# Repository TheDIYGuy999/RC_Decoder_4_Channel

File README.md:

#This is an Arduino 4 channel RC signal to DC motor converter shield
## Features:
- Reads 4 standard RC servo signals and converts them to control 4 DC motors
- Auto channel zero adjustment during setup()
- 5V / 16MHz or 3.3v / 8MHz Pro Micro or Pro Mini
- DRV8833 H-Bridge driver, controlled with my DRV8833 Arduino library
- Motor 1 & 2 can be used to drive a caterpillar vehicle:
* direct mode (2x throttle, one for each caterpillar)
* steering mode means, you have one throttle and one steering input. The speed of the inner wheel can be fully reversed, up to 100%. The vehicle then turns "in place"
* semi caterpillar mode. Same as above, but the speed of the inner wheel can only be reduced about 30%
* arrays for steering behaviour calibration, now with nonlinear mapping
* two additional motor outputs for other vehicle functions

## Usage

See pictures in this repo

(c) 2016 TheDIYGuy999

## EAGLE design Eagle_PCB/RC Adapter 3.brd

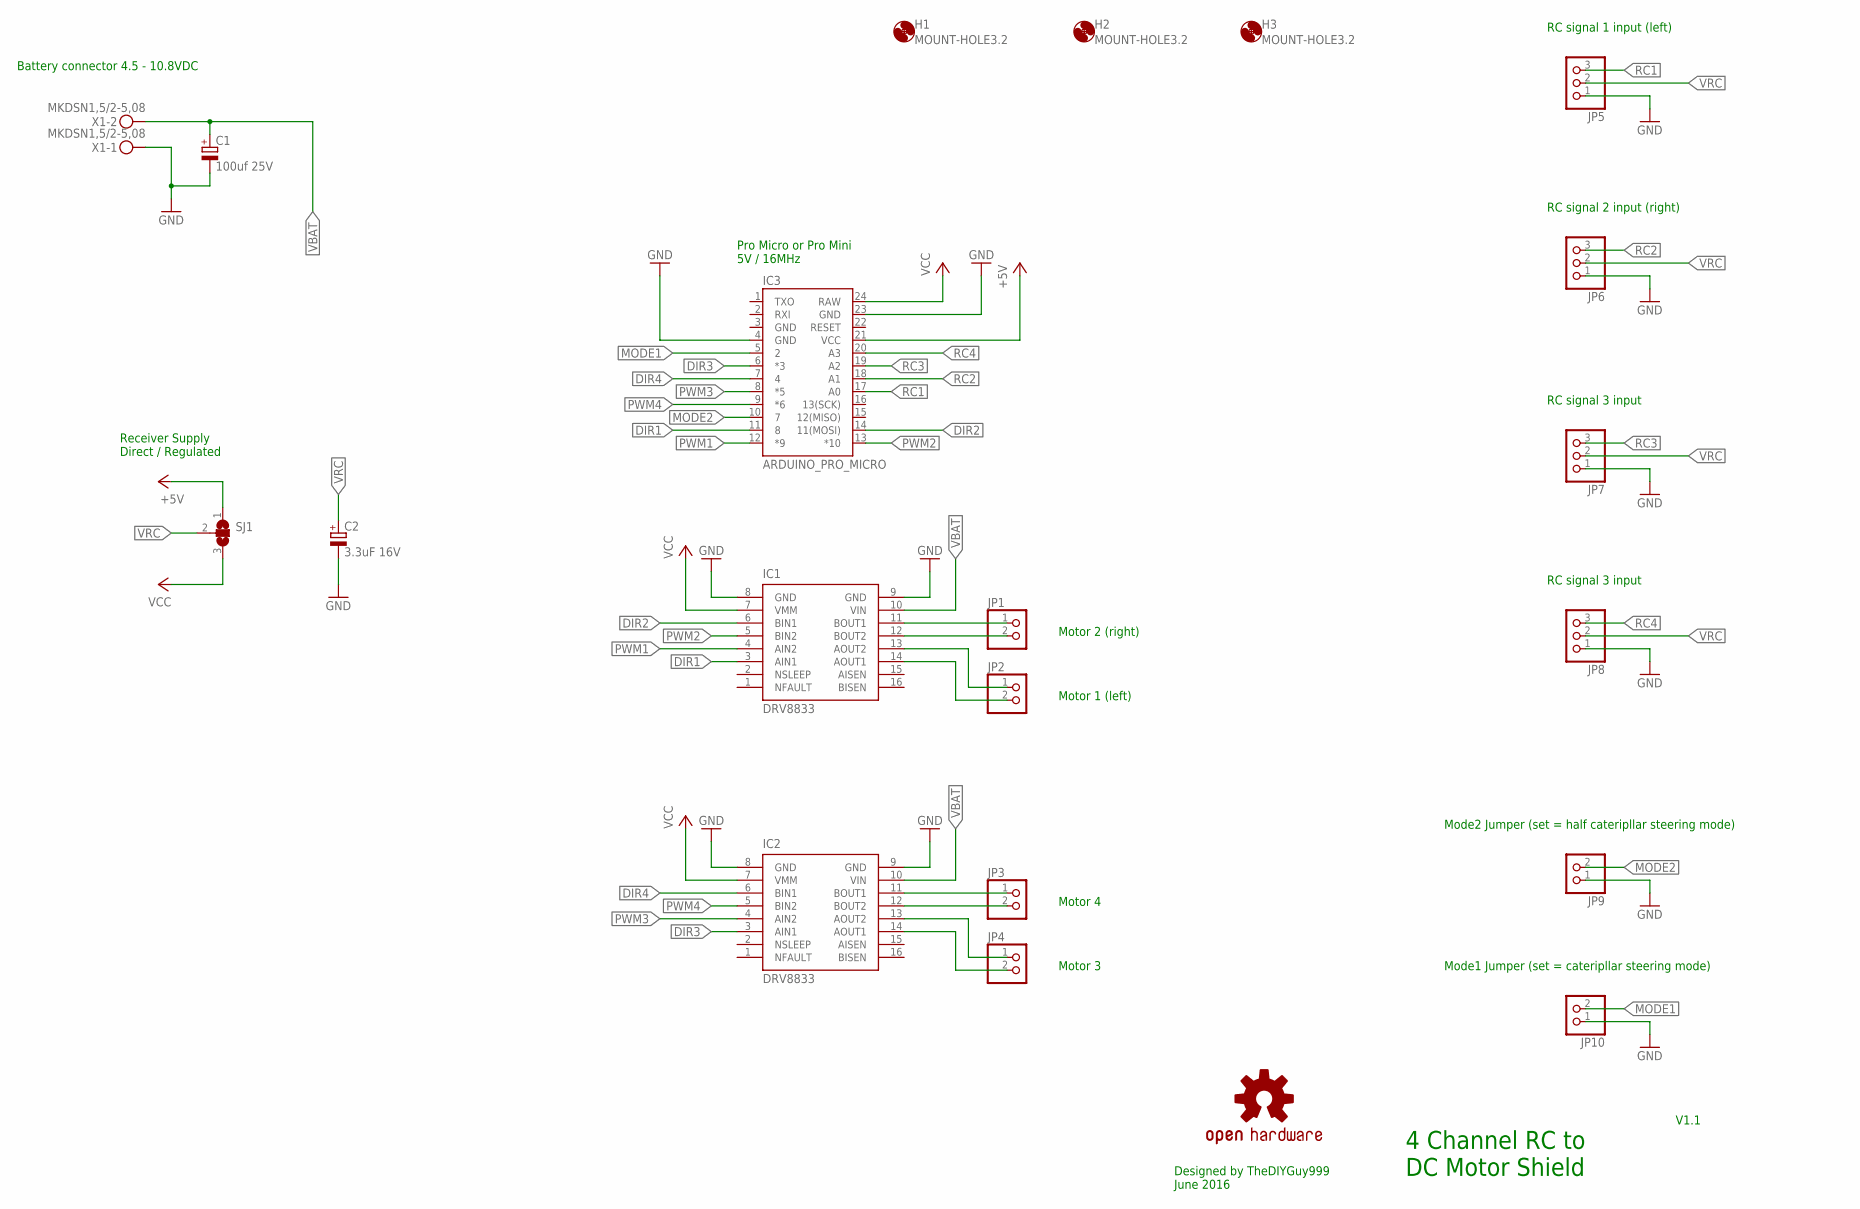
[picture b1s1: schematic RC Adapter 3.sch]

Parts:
C1: 100uf 25V; E2,5-6E
C2: 3.3uF 16V; ETR1
H1, H2, H3: MOUNT-HOLE3.2; 3,2
IC1, IC2: DRV8833
IC3: ARDUINO_PRO_MICRO
JP1, JP2, JP3, JP4, JP9, JP10: PINHD-1X2; 1X02
JP5, JP6, JP7, JP8: PINHD-1X3; 1X03
LOGO1: OSHW-LOGOL; OSHW-LOGO-L
SJ1: SJ2W; SJ_2
X1: MKDSN1,5/2-5,08

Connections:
+5V: IC3.21 (VCC), SJ1.1
DIR1: IC1.3 (AIN1), IC3.11 (8)
DIR2: IC1.6 (BIN1), IC3.14 (11(MOSI))
DIR3: IC2.3 (AIN1), IC3.6 (*3)
DIR4: IC2.6 (BIN1), IC3.7 (4)
GND: C1.-, C2.-, IC1.8 (GND), IC1.9 (GND), IC2.8 (GND), IC2.9 (GND), IC3.4 (GND), IC3.23 (GND), JP5.1, JP6.1, JP7.1, JP8.1, JP9.1, JP10.1, X1.1
MODE1: IC3.5 (2), JP10.2
MODE2: IC3.10 (7), JP9.2
unnamed: IC2.11 (BOUT1), JP3.1
unnamed: IC2.12 (BOUT2), JP3.2
unnamed: IC2.13 (AOUT2), JP4.1
unnamed: IC2.14 (AOUT1), JP4.2
unnamed: IC1.11 (BOUT1), JP1.1
unnamed: IC1.12 (BOUT2), JP1.2
unnamed: IC1.13 (AOUT2), JP2.1
unnamed: IC1.14 (AOUT1), JP2.2
PWM1: IC1.4 (AIN2), IC3.12 (*9)
PWM2: IC1.5 (BIN2), IC3.13 (*10)
PWM3: IC2.4 (AIN2), IC3.8 (*5)
PWM4: IC2.5 (BIN2), IC3.9 (*6)
RC1: IC3.17 (A0), JP5.3
RC2: IC3.18 (A1), JP6.3
RC3: IC3.19 (A2), JP7.3
RC4: IC3.20 (A3), JP8.3
VBAT: C1.+, IC1.10 (VIN), IC2.10 (VIN), X1.2
VCC: IC1.7 (VMM), IC2.7 (VMM), IC3.24 (RAW), SJ1.3
VRC: C2.+, JP5.2, JP6.2, JP7.2, JP8.2, SJ1.2

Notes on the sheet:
Pro Micro or Pro Mini 5V / 16MHz
Mode1 Jumper (set = cateripllar steering mode)
RC signal 1 input (left)
RC signal 2 input (right)
Mode2 Jumper (set = half cateripllar steering mode)
RC signal 3 input
Battery connector 4.5 - 10.8VDC
Motor 1 (left)
Motor 2 (right)
Motor 4
Motor 3
4 Channel RC to DC Motor Shield
Receiver Supply Direct / Regulated
V1.1
Designed by TheDIYGuy999 June 2016

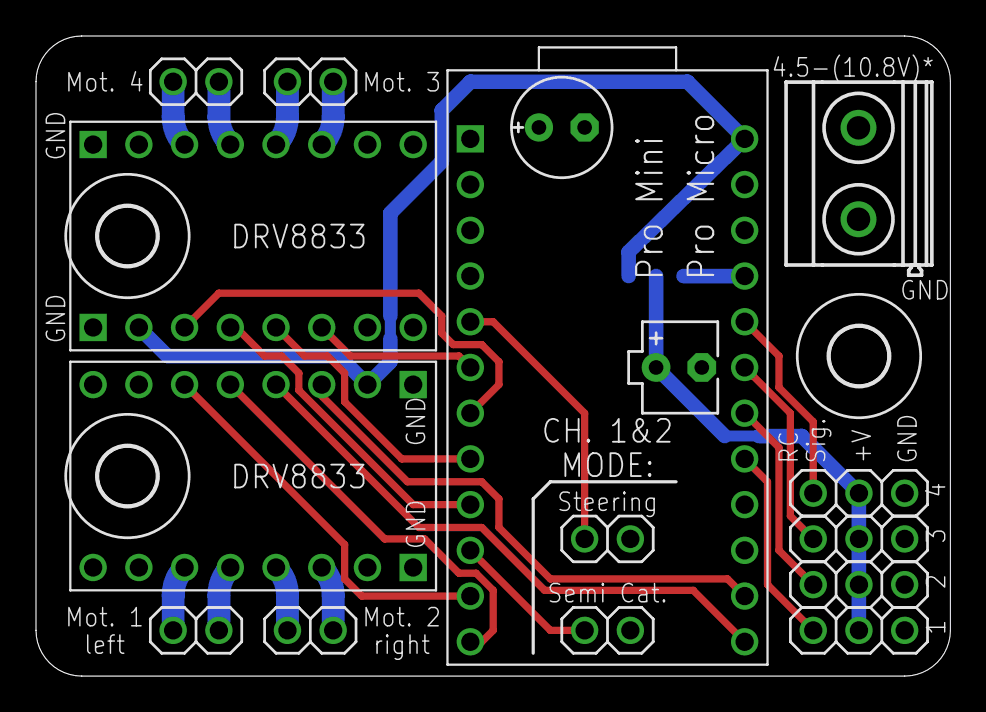
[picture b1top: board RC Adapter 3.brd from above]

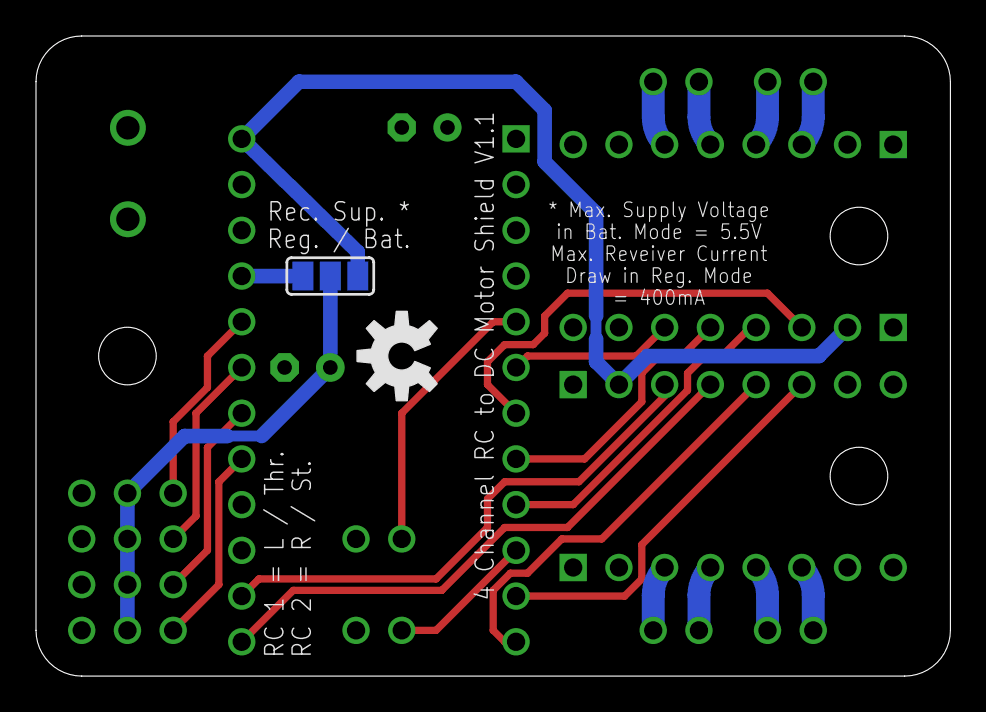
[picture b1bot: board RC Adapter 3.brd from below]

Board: 2 copper layers, 50.8 x 35.6 mm, 22 parts (2 on the bottom side), 27 nets.

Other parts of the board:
U$1: OSHW-LOGO-M

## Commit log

2016-06-20 Updated to V1.1
    Now also compatible with a Pro Mini
2016-06-25 Steering calibration arrays added
2016-06-28 Steering arrays now with nonlinear mapping
2016-06-29 Automatic pin change for Pro Mini
2016-06-29 Typos
2016-08-06 Application example added

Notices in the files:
parts and their libraries:
SparkFun-Aesthetics: Licensing: Creative Commons ShareAlike 4.0 International - https://creativecommons.org/licenses/by-sa/4.0
